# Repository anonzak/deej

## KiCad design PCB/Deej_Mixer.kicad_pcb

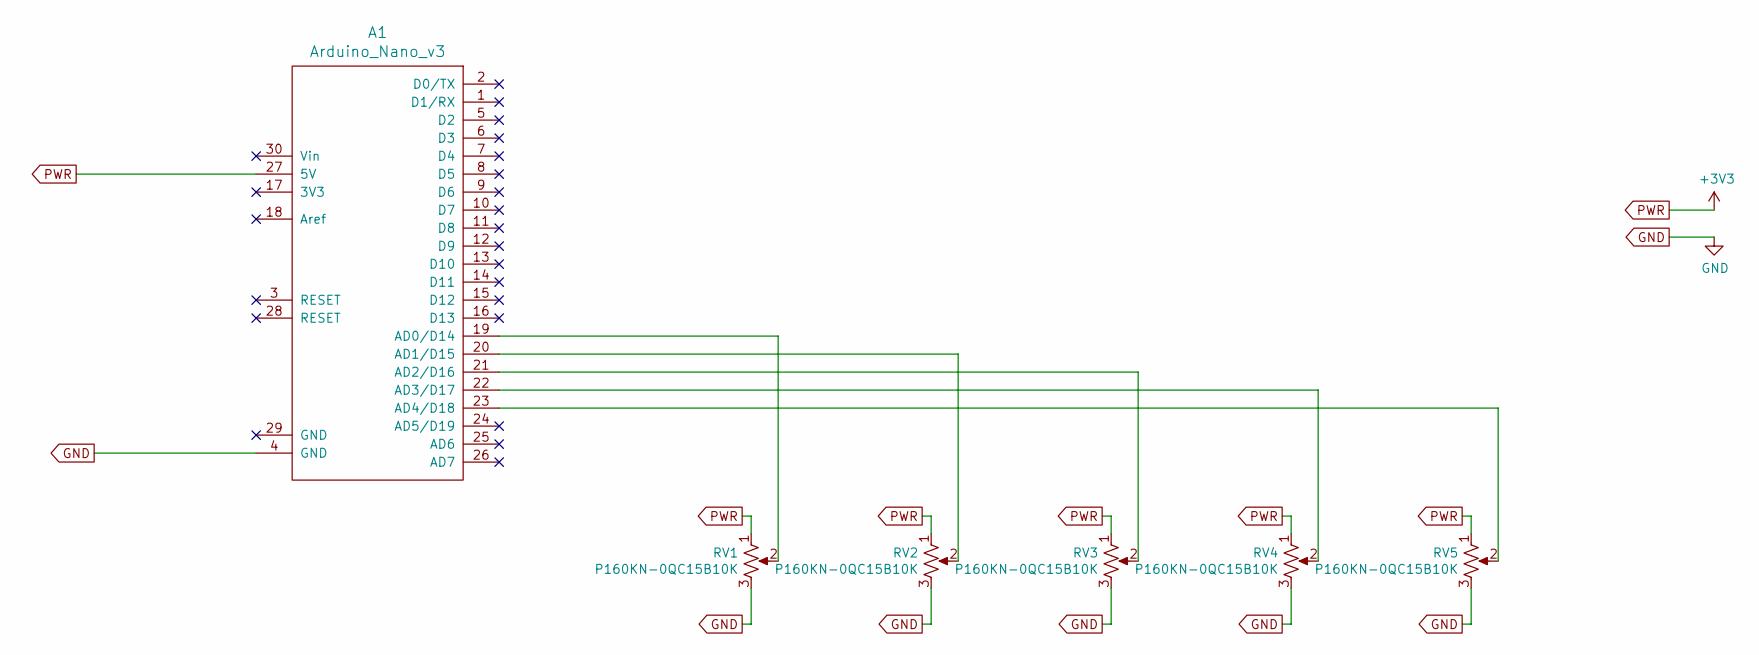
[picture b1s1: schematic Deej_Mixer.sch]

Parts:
A1: Arduino_Nano_v3; arduino_nano
RV1, RV2, RV3, RV4, RV5: P160KN-0QC15B10K; P160KN

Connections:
GND: A1.4 (GND), RV1.3, RV2.3, RV3.3, RV4.3, RV5.3
unnamed: A1.19 (AD0/D14), RV1.2
unnamed: A1.20 (AD1/D15), RV2.2
unnamed: A1.21 (AD2/D16), RV3.2
unnamed: A1.22 (AD3/D17), RV4.2
unnamed: A1.23 (AD4/D18), RV5.2
PWR: A1.27 (5V), RV1.1, RV2.1, RV3.1, RV4.1, RV5.1

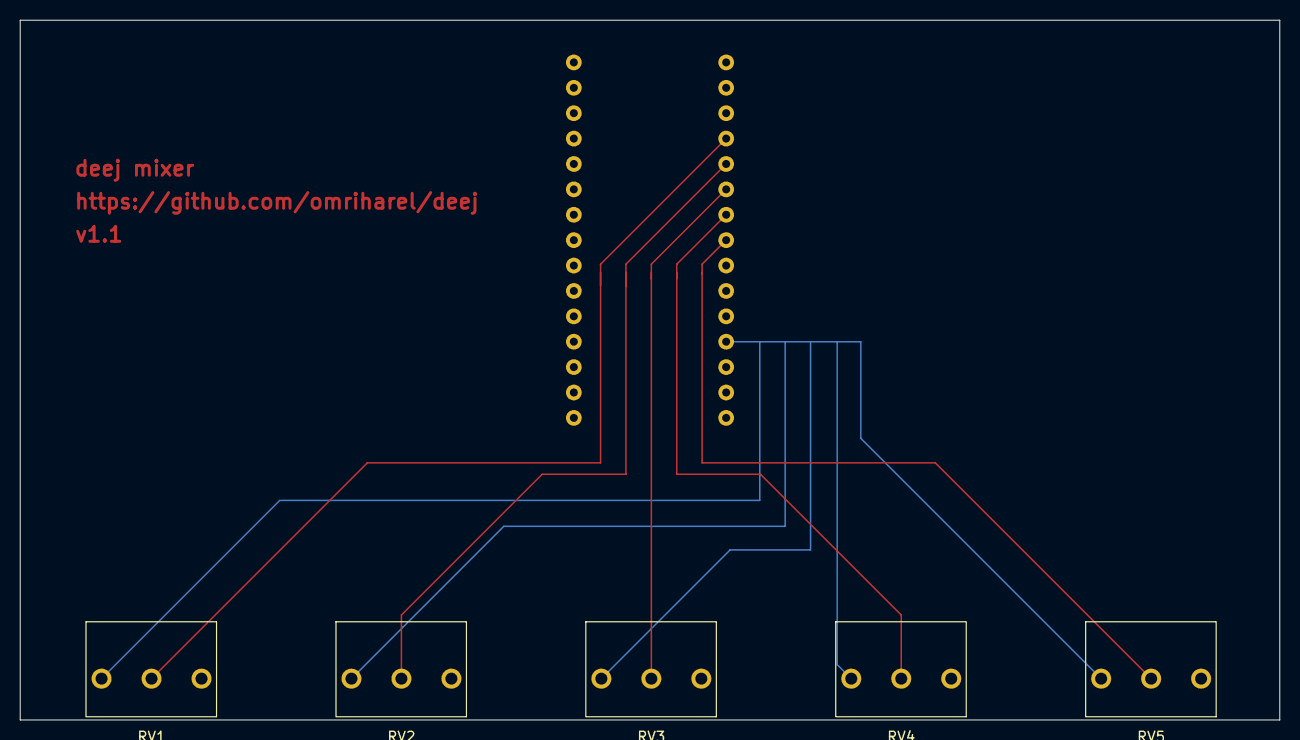
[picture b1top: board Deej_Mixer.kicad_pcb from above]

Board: 2 copper layers, 126.0 x 70.0 mm, 6 parts (1 on the bottom side), 7 nets.

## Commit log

2023-09-18 Adding old work to clean up PC
